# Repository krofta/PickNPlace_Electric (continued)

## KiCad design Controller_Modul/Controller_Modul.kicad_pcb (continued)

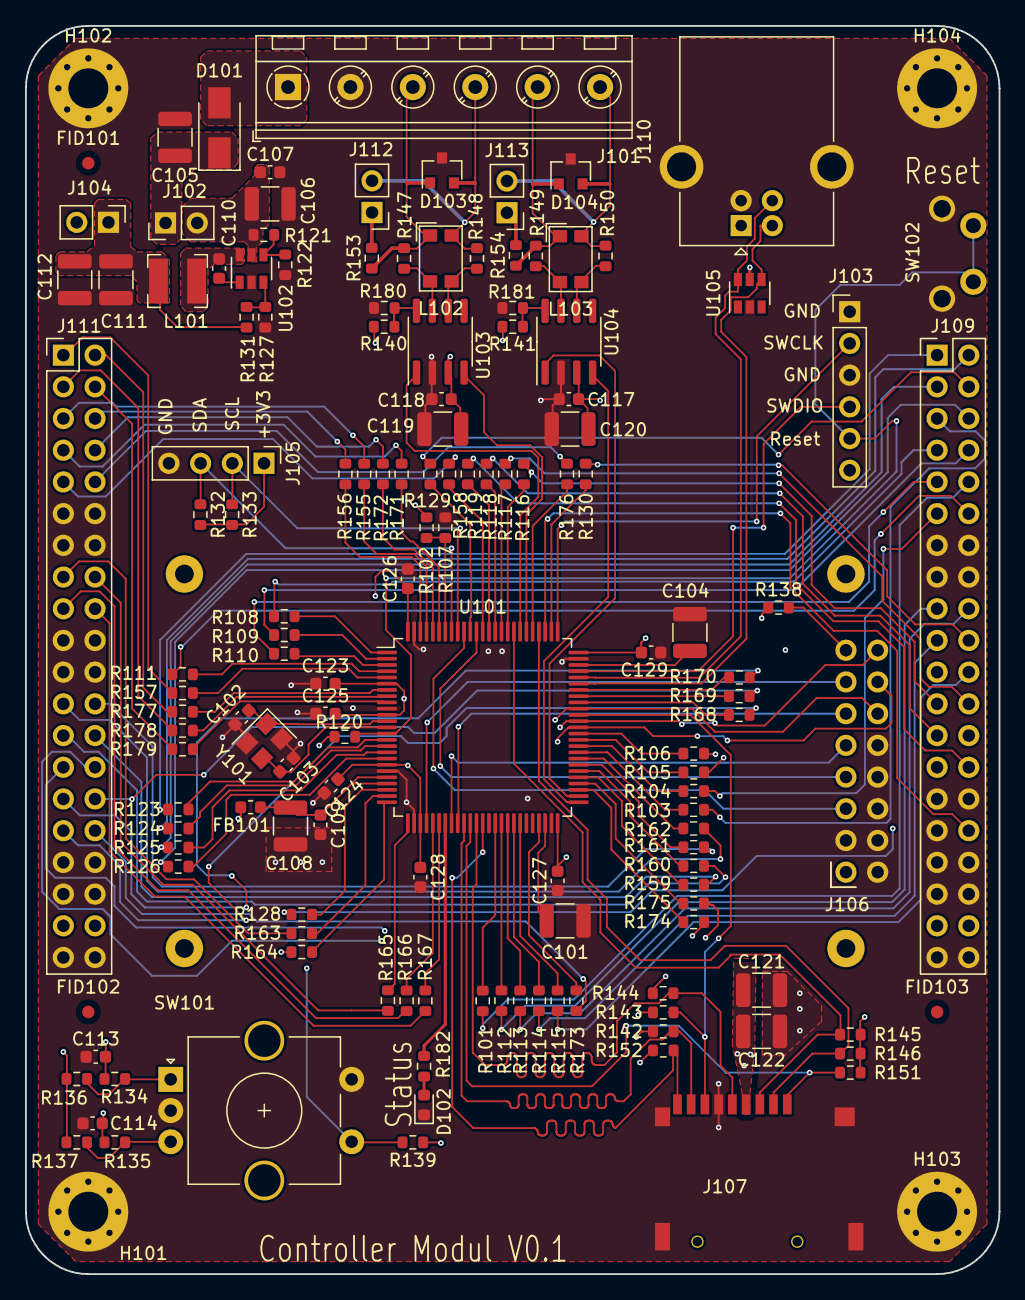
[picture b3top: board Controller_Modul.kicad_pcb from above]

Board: 4 copper layers, 78.0 x 100.0 mm, 147 parts (0 on the bottom side), 158 nets.

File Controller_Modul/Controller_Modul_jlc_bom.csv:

Comment,Designator,Footprint,LCSC Part #
"2.2u 50V Unpolarized capacitor, small symbol","C101,C104",C_1210_3225Metric, C696854 
"18p 50V Unpolarized capacitor, small symbol","C102,C103",C_0603_1608Metric,C258467
"10u 50V Unpolarized capacitor, small symbol","C105,C106,C108,C111,C112,C121,C122",C_1210_3225Metric,C1849
"100n 50V Unpolarized capacitor, small symbol","C107,C109,C110,C123,C124,C125,C126,C127,C128,C129",C_0603_1608Metric,C282519
"100n Unpolarized capacitor, small symbol","C113,C114,C117,C118",C_0603_1608Metric,C83060
"10u Unpolarized capacitor, small symbol","C119,C120",C_1210_3225Metric,C1849
"SS22F-SS2200F Schottky diode, small symbol",D101,D_SMA,C190803
"70R Ferrite bead, small symbol",FB101,L_0603_1608Metric,C513774
"Screw_Terminal_01x06 Generic screw terminal, single row, 01x06, script generated (kicad-library-utils/schlib/autogen/connector/)",J101,TerminalBlock_RND_205-00049_1x06_P5.00mm_Horizontal,C8475
"Conn_02x01 Generic connector, double row, 02x01, this symbol is compatible with counter-clockwise, top-bottom and odd-even numbering schemes., script generated (kicad-library-utils/schlib/autogen/connector/)","J102,J104,J112,J113",PinHeader_1x02_P2.54mm_Vertical,C358684
"Conn_01x08_Male Generic connector, double row, 02x08, top/bottom pin numbering scheme (row 1: 1...pins_per_row, row2: pins_per_row+1 ... num_pins), script generated (kicad-library-utils/schlib/autogen/connector/)",J106,ST7789_Waveshare2,C3406
Micro_SD_Card_Det Micro SD Card Socket with card detection pins,J107,TF-115-BCP9,C720505
IPC 16P ,J108,Empty,C8372
"Conn_02x20_Odd_Even Generic connector, double row, 02x20, odd/even pin numbering scheme (row 1 odd numbers, row 2 even numbers), script generated (kicad-library-utils/schlib/autogen/connector/)","J109,J111",PinHeader_2x20_P2.54mm_Vertical,C601944
USB_B_Mini USB Type B connector,J110,USB_B_OST_USB-B1HSxx_Horizontal,C46392
IPC 40P ,"J114,J115",Empty,C601933
"12u  SRN4018 Inductor, small symbol",L101,L_Bourns-SRN4018,C354591 
"1K Resistor, small symbol","R101,R103,R104,R105,R106,R108,R109,R110,R111,R112,R113,R114,R115,R116,R117,R118,R119,R123,R124,R125,R126,R128,R129,R130,R132,R133,R136,R137,R138,R139,R140,R141,R155,R156,R157,R158,R159,R160,R161,R162,R163,R164,R165,R166,R167,R168,R169,R170,R171,R172,R173,R174,R175,R176,R177,R178,R179",R_0603_1608Metric,C14676
"10K Resistor, small symbol","R107,R120,R134,R135,R152",R_0603_1608Metric,C99198
"51K Resistor, small symbol","R121,R122,R131",R_0603_1608Metric,C384211
"22K1 Resistor, small symbol","R127,R142,R143,R144,R145,R146,R151",R_0603_1608Metric,C137768
"0R Resistor, small symbol","R147,R148,R149,R150",R_0603_1608Metric,C384298
"120R Resistor, small symbol","R153,R154",R_0603_1608Metric,C114681
TPS560430 ,U102,SOT-23-6,C524782
"SN65HVD230 CAN Bus Transceivers, 3.3V, 1Mbps, Low-Power capabilities, SOIC-8","U103,U104",SOIC-8_3.9x4.9mm_P1.27mm,C12084
"SRV05-4 ESD Protection Diodes with Low Clamping Voltage, SOT-23-6",U105,SOT-23-6,C316033
"8MHz Four pin crystal, GND on pins 2 and 4",Y101,Crystal_SMD_3225-4Pin_3.2x2.5mm,C400090

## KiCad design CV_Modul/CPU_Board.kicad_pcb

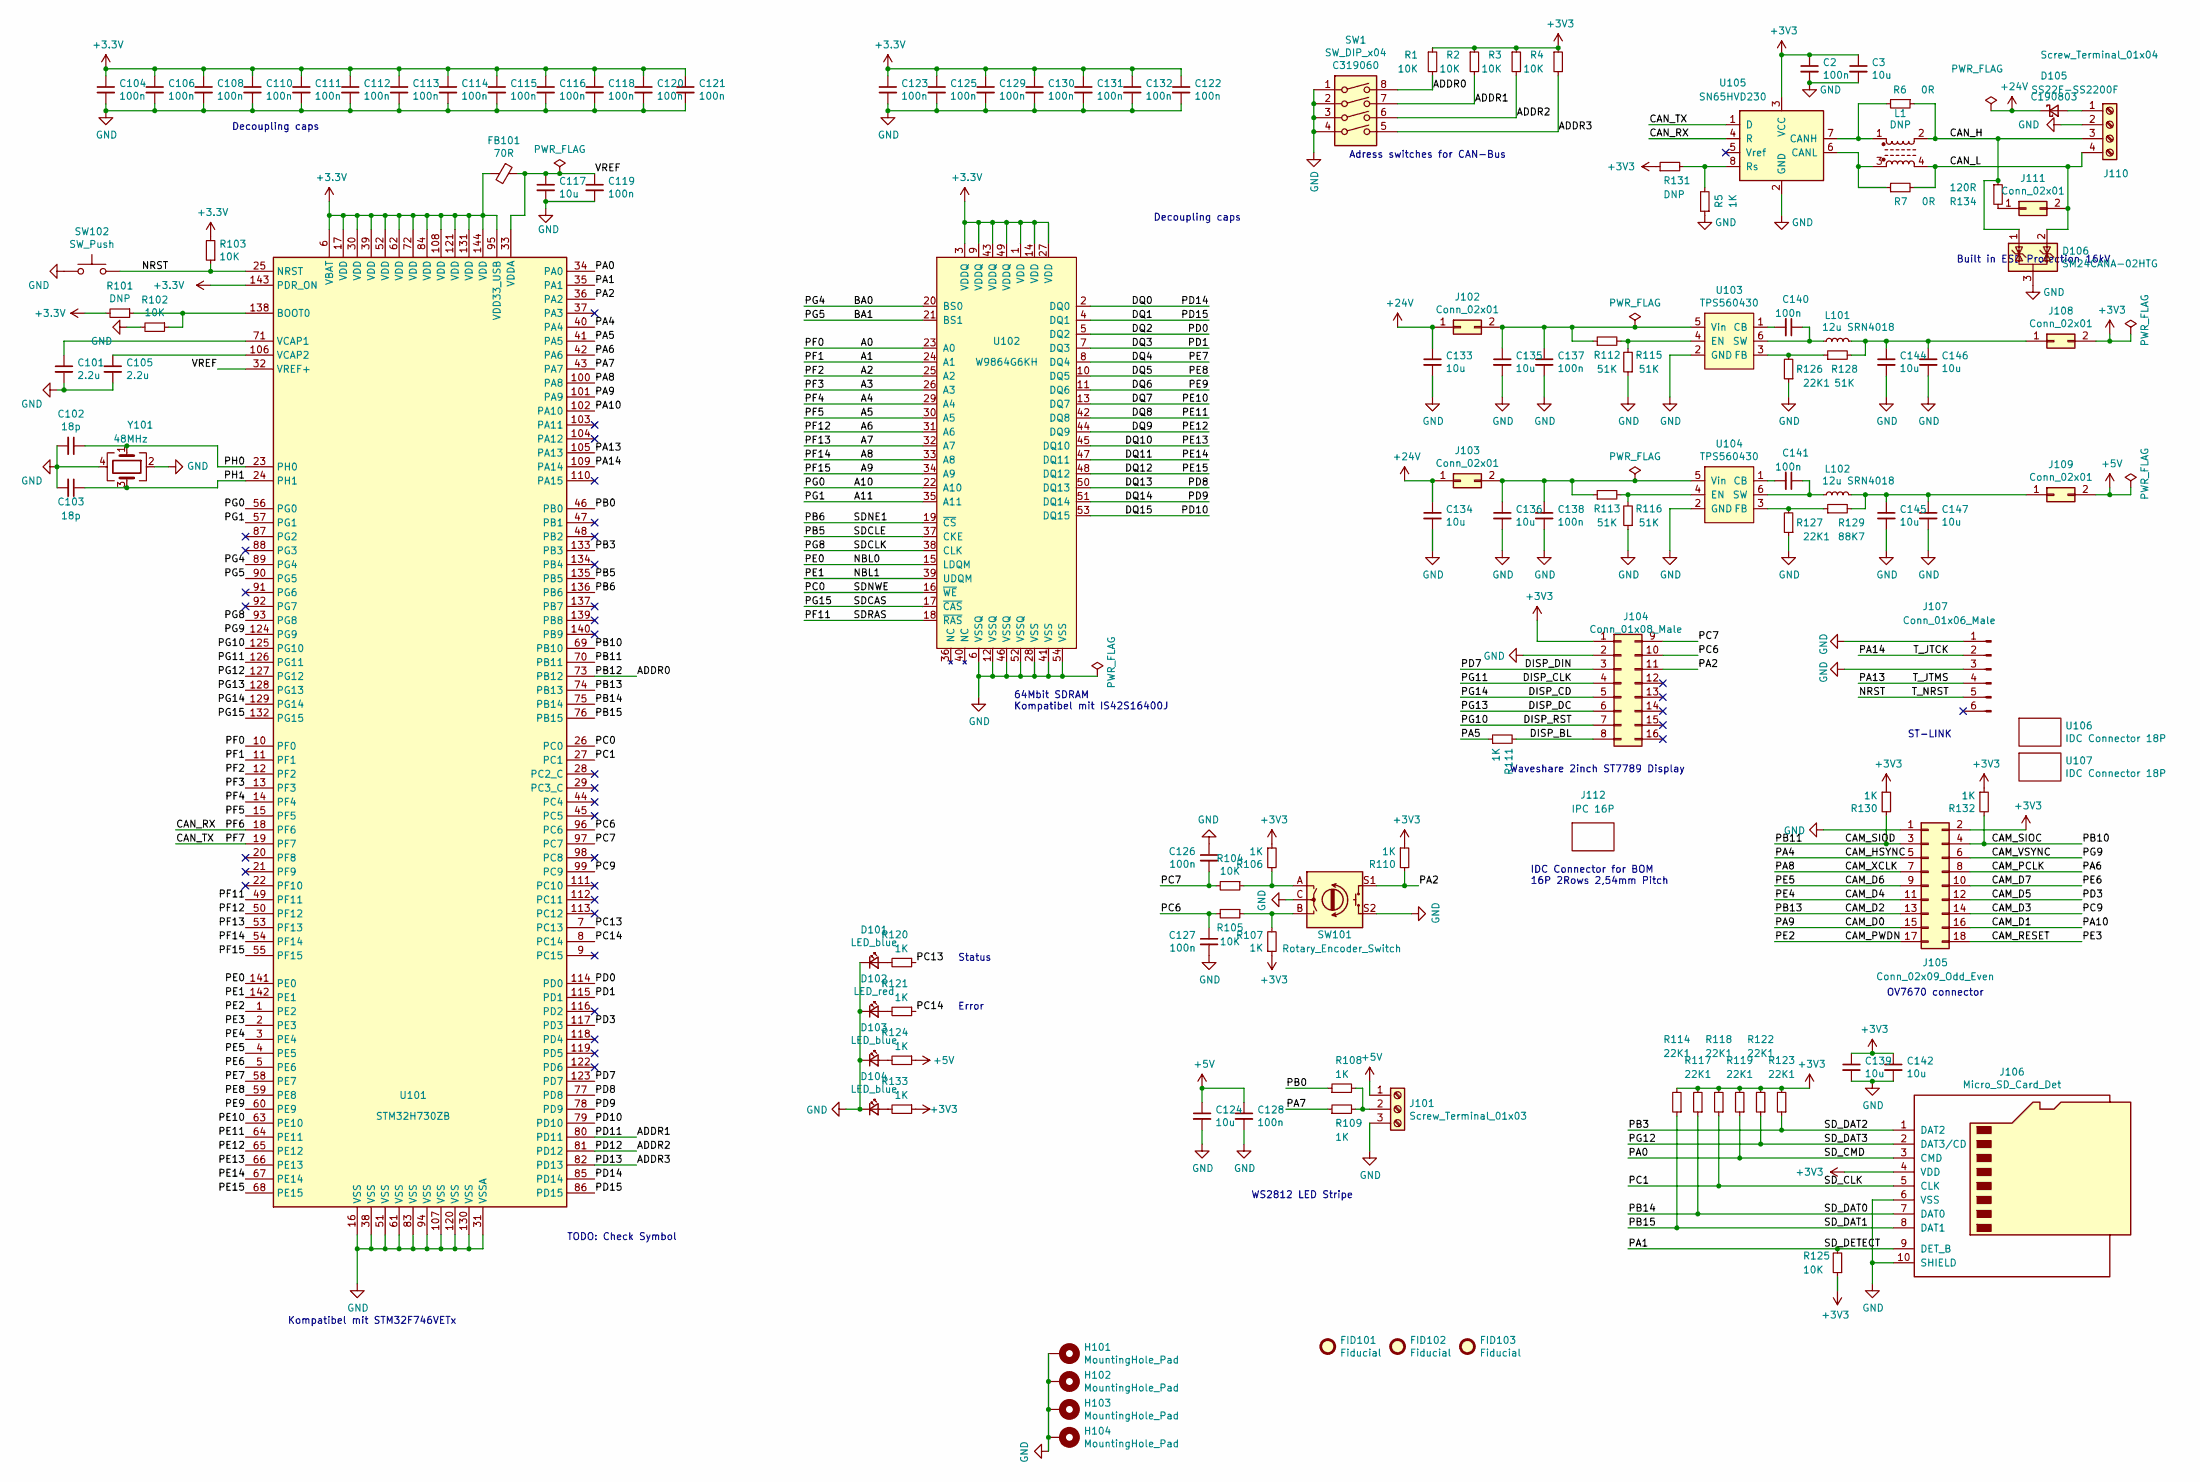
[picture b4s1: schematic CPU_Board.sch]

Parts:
C2, C104, C106, C108, C110, C111, C112, C113, C114, C115, C116, C118, C119, C120, C121, C122, C123, C125, C126, C127, C128, C129, C130, C131, C132, C137, C138, C140, C141: 100n; C_0603_1608Metric; LCSC C83060
C3, C117, C124, C133, C134, C135, C136, C139, C142, C144, C145, C146, C147: 10u; C_1210_3225Metric; LCSC C1849
C101, C105: 2.2u; C_1210_3225Metric; LCSC C696854
C102, C103: 18p; C_0603_1608Metric; LCSC C258467
D101, D103, D104: LED_blue; LED_0603_1608Metric; LCSC C193191
D102: LED_red; LED_0603_1608Metric; LCSC C205445
D105: SS22F-SS2200F; D_SMA; LCSC C190803
D106: SM24CANA-02HTG; SOT-23; LCSC C151236
FB101: 70R; L_0603_1608Metric; LCSC C513774
FID101, FID102, FID103: Fiducial; Fiducial_1mm_Mask2mm; LCSC 0
H101, H102, H103, H104: MountingHole_Pad; MountingHole_3.2mm_M3_Pad_Via; LCSC 0
J101: Screw_Terminal_01x03; TerminalBlock_RND_205-00046_1x03_P5.00mm_Horizontal; LCSC C8401
J102, J103, J108, J109, J111: Conn_02x01; PinHeader_1x02_P2.54mm_Vertical; LCSC 0
J104: Conn_01x08_Male; ST7789_Waveshare; LCSC 0
J105: Conn_02x09_Odd_Even; PinHeader_2x09_P2.54mm_Vertical; LCSC C11216
J106: Micro_SD_Card_Det; TF-115-BCP9; LCSC C720505
J107: Conn_01x06_Male; PinHeader_1x06_P2.54mm_Vertical; LCSC 0
J110: Screw_Terminal_01x04; TerminalBlock_RND_205-00047_1x04_P5.00mm_Horizontal; LCSC C8475
J112: IPC 16P; Empty; LCSC C8372
L1: DNP; L_CommonModeChoke_Coilcraft_1812CAN; LCSC 0
L101, L102: 12u SRN4018; L_Bourns-SRN4018; LCSC C354591
R1, R2, R3, R4, R102, R103, R104, R105, R125: 10K; R_0603_1608Metric; LCSC C99198
R5, R106, R107, R108, R109, R110, R111, R120, R121, R124, R130, R132, R133: 1K; R_0603_1608Metric; LCSC C14676
R6, R7: 0R; R_0603_1608Metric; LCSC C384298
R101, R131: DNP; R_0603_1608Metric; LCSC 0
R112, R113, R115, R116, R128: 51K; R_0603_1608Metric; LCSC C384211
R114, R117, R118, R119, R122, R123, R126, R127: 22K1; R_0603_1608Metric; LCSC C137768
R129: 88K7; R_0603_1608Metric; LCSC C163418
R134: 120R; R_0603_1608Metric; LCSC C114681
SW1: SW_DIP_x04; SW_DIP_SPSTx04_Slide_6.7x11.72mm_W7.62mm_P2.54mm_LowProfile; LCSC C319060
SW101: Rotary_Encoder_Switch; RotaryEncoder_Alps_EC11E-Switch_Vertical_H20mm_CircularMoun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; LCSC 0
SW102: SW_Push; TactileSwitchLCSC; LCSC C455137
U101: STM32H730ZB; LQFP-144_20x20mm_P0.5mm; LCSC 0
U102: W9864G6KH; TSOP-II-54_22.2x10.16mm_P0.8mm; LCSC C62378
U103, U104: TPS560430; SOT-23-6; LCSC C524782
U105: SN65HVD230; SOIC-8_3.9x4.9mm_P1.27mm; LCSC C12084
U106, U107: IDC Connector 18P; Empty; LCSC C376143
Y101: 48MHz; Crystal_SMD_3225-4Pin_3.2x2.5mm; LCSC C389928

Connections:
+5V: C124.1, C128.1, J101.1, J109.2, R124.1
+24V: C133.1, C134.1, D105.1 (K), J102.1, J103.1
/A0: U101.10 (PF0), U102.23 (A0)
/A1: U101.11 (PF1), U102.24 (A1)
/A2: U101.12 (PF2), U102.25 (A2)
/A3: U101.13 (PF3), U102.26 (A3)
/A4: U101.14 (PF4), U102.29 (A4)
/A5: U101.15 (PF5), U102.30 (A5)
/A6: U101.50 (PF12), U102.31 (A6)
/A7: U101.53 (PF13), U102.32 (A7)
/A8: U101.54 (PF14), U102.33 (A8)
/A9: U101.55 (PF15), U102.34 (A9)
/A10: U101.56 (PG0), U102.22 (A10)
/A11: U101.57 (PG1), U102.35 (A11)
/ADDR0: R1.2, SW1.8, U101.73 (PB12)
/ADDR1: R2.2, SW1.7, U101.80 (PD11)
/ADDR2: R3.2, SW1.6, U101.81 (PD12)
/ADDR3: R4.2, SW1.5, U101.82 (PD13)
/BA0: U101.89 (PG4), U102.20 (BS0)
/BA1: U101.90 (PG5), U102.21 (BS1)
/CAM_D0: J105.15, U101.101 (PA9)
/CAM_D1: J105.16, U101.102 (PA10)
/CAM_D2: J105.13, U101.74 (PB13)
/CAM_D3: J105.14, U101.99 (PC9)
/CAM_D4: J105.11, U101.3 (PE4)
/CAM_D5: J105.12, U101.117 (PD3)
/CAM_D6: J105.9, U101.4 (PE5)
/CAM_D7: J105.10, U101.5 (PE6)
/CAM_HSYNC: J105.5, U101.40 (PA4)
/CAM_PCLK: J105.8, U101.42 (PA6)
/CAM_PWDN: J105.17, U101.1 (PE2)
/CAM_RESET: J105.18, U101.2 (PE3)
/CAM_SIOC: J105.4, R132.2, U101.69 (PB10)
/CAM_SIOD: J105.3, R130.2, U101.70 (PB11)
/CAM_VSYNC: J105.6, U101.124 (PG9)
/CAM_XCLK: J105.7, U101.100 (PA8)
/CAN_H: D106.1 (K), J110.3, L1.2, R6.1, R134.1
/CAN_L: D106.2 (K), J110.4, J111.2, L1.4, R7.2
/CAN_RX: U101.18 (PF6), U105.4 (R)
/CAN_TX: U101.19 (PF7), U105.1 (D)
/DISP_BL: J104.8, R111.2
/DISP_CD: J104.5, U101.129 (PG14)
/DISP_CLK: J104.4, U101.126 (PG11)
/DISP_DC: J104.6, U101.128 (PG13)
/DISP_DIN: J104.3, U101.123 (PD7)
/DISP_RST: J104.7, U101.125 (PG10)
/DQ0: U101.85 (PD14), U102.2 (DQ0)
/DQ1: U101.86 (PD15), U102.4 (DQ1)
/DQ2: U101.114 (PD0), U102.5 (DQ2)
/DQ3: U101.115 (PD1), U102.7 (DQ3)
/DQ4: U101.58 (PE7), U102.8 (DQ4)
/DQ5: U101.59 (PE8), U102.10 (DQ5)
/DQ6: U101.60 (PE9), U102.11 (DQ6)
/DQ7: U101.63 (PE10), U102.13 (DQ7)
/DQ8: U101.64 (PE11), U102.42 (DQ8)
/DQ9: U101.65 (PE12), U102.44 (DQ9)
/DQ10: U101.66 (PE13), U102.45 (DQ10)
/DQ11: U101.67 (PE14), U102.47 (DQ11)
/DQ12: U101.68 (PE15), U102.48 (DQ12)
/DQ13: U101.77 (PD8), U102.50 (DQ13)
/DQ14: U101.78 (PD9), U102.51 (DQ14)
/DQ15: U101.79 (PD10), U102.53 (DQ15)
/NBL0: U101.141 (PE0), U102.15 (LDQM)
/NBL1: U101.142 (PE1), U102.39 (UDQM)
/NRST: J107.5, R103.1, SW102.2, U101.25 (NRST)
/PA0: J106.3 (CMD), R119.1, U101.34 (PA0)
/PA1: J106.9 (DET_B), R125.2, U101.35 (PA1)
/PA2: J104.11, R110.2, SW101.S1, U101.36 (PA2)
/PA5: R111.1, U101.41 (PA5)
/PA7: R109.1, U101.43 (PA7)
/PA13: J107.4, U101.105 (PA13)
/PA14: J107.2, U101.109 (PA14)
/PB0: R108.1, U101.46 (PB0)
/PB3: J106.1 (DAT2), R123.1, U101.133 (PB3)
/PB5: U101.135 (PB5), U102.37 (CKE)
/PB6: U101.136 (PB6), U102.19 (~CS)
/PB14: J106.7 (DAT0), R117.1, U101.75 (PB14)
/PB15: J106.8 (DAT1), R114.1, U101.76 (PB15)
/PC0: U101.26 (PC0), U102.16 (~WE)
/PC1: J106.5 (CLK), R118.1, U101.27 (PC1)
/PC6: C127.1, J104.10, R105.2, U101.96 (PC6)
/PC7: C126.2, J104.9, R104.2, U101.97 (PC7)
/PC13: R120.1, U101.7 (PC13)
/PC14: R121.1, U101.8 (PC14)
/PF11: U101.49 (PF11), U102.18 (~RAS)
/PG8: U101.93 (PG8), U102.38 (CLK)
/PG12: J106.2 (DAT3/CD), R122.1, U101.127 (PG12)
/PG15: U101.132 (PG15), U102.17 (~CAS)
/PH0: C102.1, U101.23 (PH0), Y101.1
/PH1: C103.1, U101.24 (PH1), Y101.3
/VREF: C117.1, C119.1, FB101.1, U101.32 (VREF+), U101.33 (VDDA)
GND: C2.2, C3.2, C101.2, C102.2, C103.2, C104.2, C105.2, C106.2, C108.2, C110.2, C111.2, C112.2, C113.2, C114.2, C115.2, C116.2, C117.2, C118.2, C119.2, C120.2, C121.2, C122.2, C123.2, C124.2, C125.2, C126.1, C127.2, C128.2, C129.2, C130.2, C131.2, C132.2, C133.2, C134.2, C135.2, C136.2, C137.2, C138.2, C139.2, C142.2, C144.2, C145.2, C146.2, C147.2, D101.1 (K), D102.1 (K), D103.1 (K), D104.1 (K), D106.3 (A), H101.1, H102.1, H103.1, H104.1, J101.3, J104.2, J105.1, J106.6 (VSS), J106.10 (SHIELD), J107.1, J107.3, J110.2, R5.1, R102.2, R115.1, R116.1, R126.1, R127.1, SW1.1, SW1.2, SW1.3, SW1.4, SW101.C, SW101.S2, SW102.1, U101.16 (VSS), U101.31 (VSSA), U101.38 (VSS), U101.51 (VSS), U101.61 (VSS), U101.83 (VSS), U101.94 (VSS), U101.107 (VSS), U101.120 (VSS), U101.130 (VSS), U102.6 (VSSQ), U102.12 (VSSQ), U102.28 (VSS), U102.41 (VSS), U102.46 (VSSQ), U102.52 (VSSQ), U102.54 (VSS), U103.2 (GND), U104.2 (GND), U105.2 (GND), Y101.2, Y101.4
unnamed: C101.1, U101.71 (VCAP1)
unnamed: C105.1, U101.106 (VCAP2)
unnamed: C135.1, C137.1, J102.2, R112.1, U103.5 (Vin)
unnamed: C136.1, C138.1, J103.2, R113.1, U104.5 (Vin)
unnamed: C140.1, L101.1, U103.6 (SW)
unnamed: C140.2, U103.1 (CB)
unnamed: C141.1, L102.1, U104.6 (SW)
unnamed: C141.2, U104.1 (CB)
unnamed: C144.1, C146.1, J108.1, L101.2, R128.2
unnamed: C145.1, C147.1, J109.1, L102.2, R129.2
unnamed: D101.2 (A), R120.2
unnamed: D102.2 (A), R121.2
unnamed: D103.2 (A), R124.2
unnamed: D104.2 (A), R133.2
unnamed: D105.2 (A), J110.1
unnamed: J101.2, R108.2, R109.2
unnamed: J111.1, R134.2
unnamed: L1.1, R6.2, U105.7 (CANH)
unnamed: L1.3, R7.1, U105.6 (CANL)
unnamed: R101.1, R102.1, U101.138 (BOOT0)
unnamed: R104.1, R106.2, SW101.A
unnamed: R105.1, R107.2, SW101.B
unnamed: R112.2, R115.2, U103.4 (EN)
unnamed: R113.2, R116.2, U104.4 (EN)
unnamed: R126.2, R128.1, U103.3 (FB)
unnamed: R127.2, R129.1, U104.3 (FB)
unnamed: R5.2, R131.2, U105.8 (Rs)

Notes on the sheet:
64Mbit SDRAM Kompatibel mit IS42S16400J
Kompatibel mit STM32F746VETx
TODO: Check Symbol
Decoupling caps
ST-LINK
OV7670 connector
Waveshare 2inch ST7789 Display
WS2812 LED Stripe
Status
Error
Adress switches for CAN-Bus
Built in ESD Protection 16kV
IDC Connector for BOM 16P 2Rows 2,54mm Pitch

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
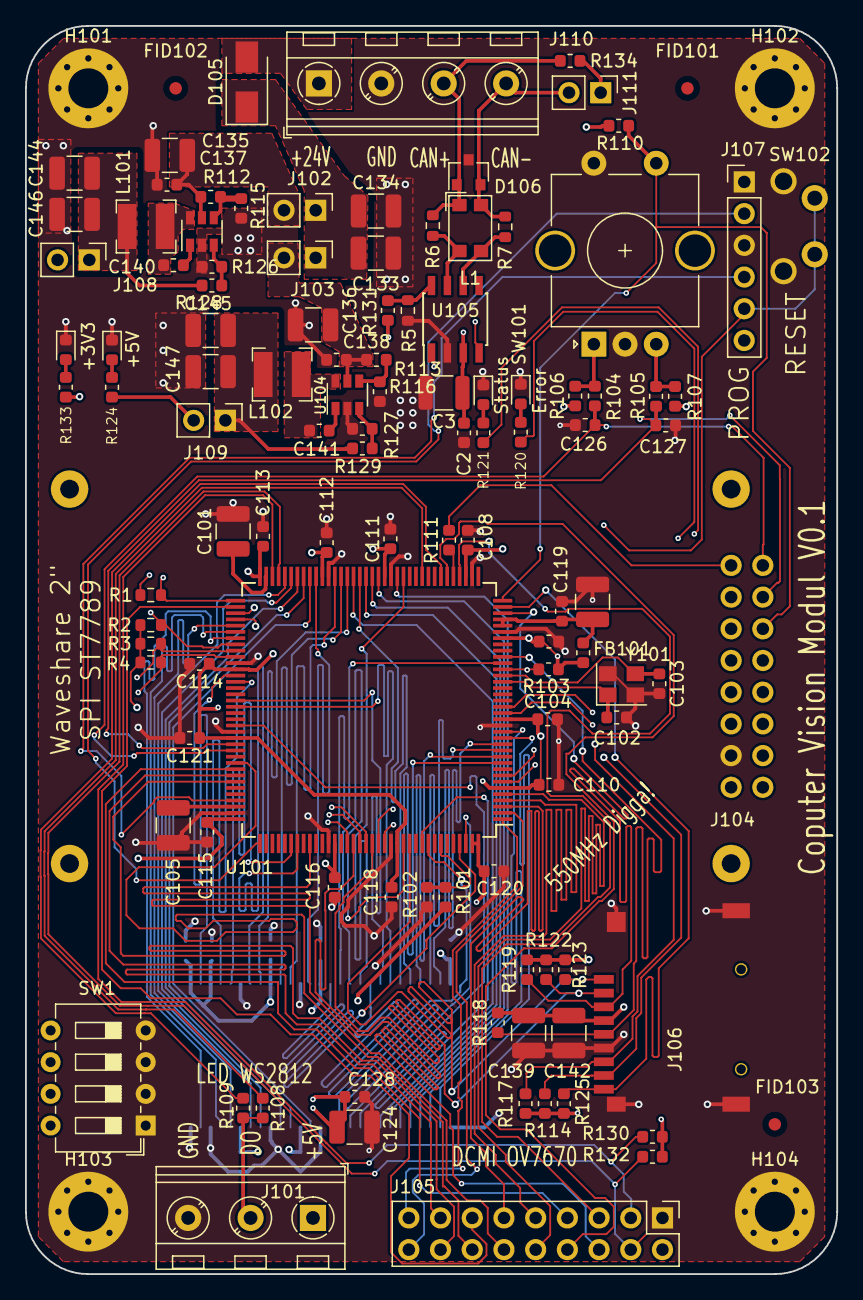
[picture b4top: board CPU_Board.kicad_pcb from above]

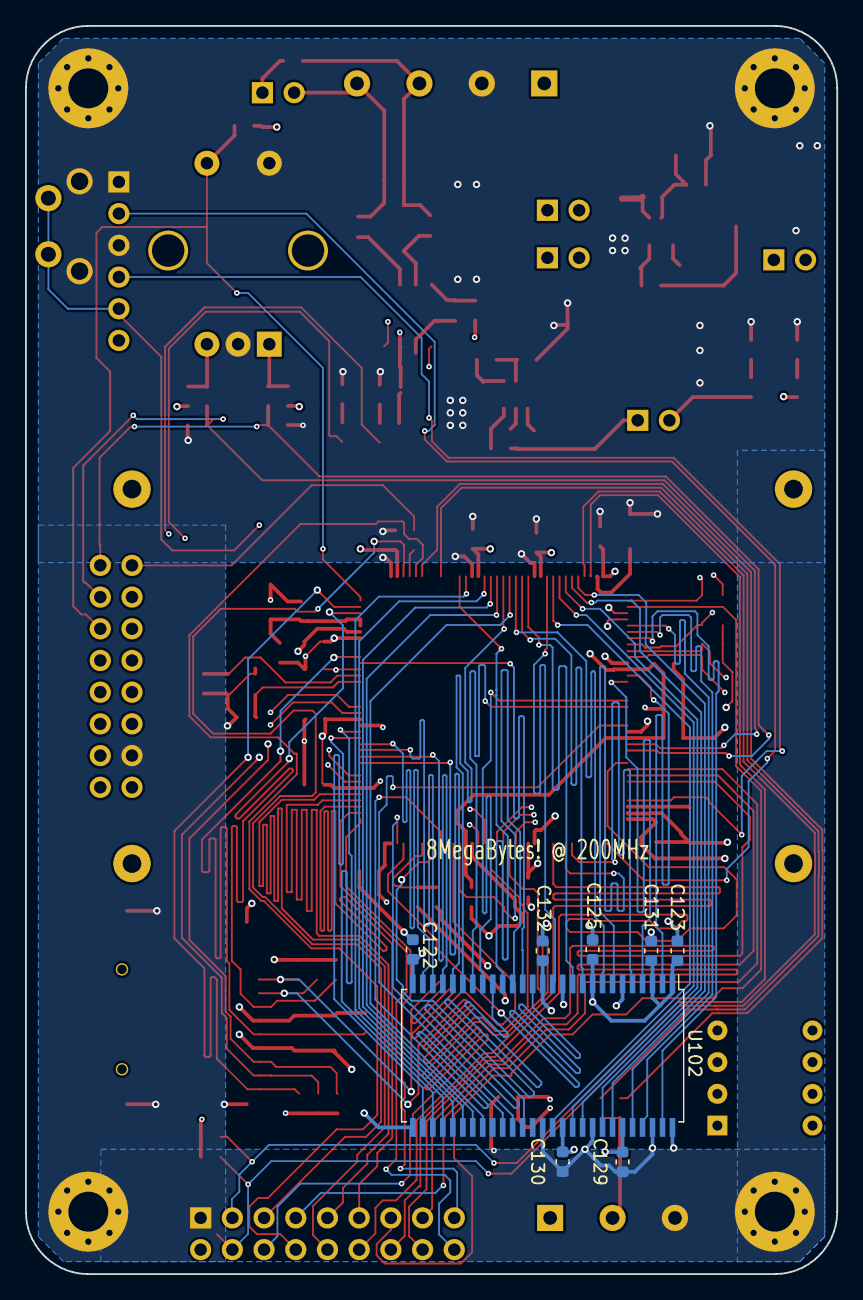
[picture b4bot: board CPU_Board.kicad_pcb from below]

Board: 4 copper layers, 65.0 x 100.0 mm, 127 parts (8 on the bottom side), 120 nets.

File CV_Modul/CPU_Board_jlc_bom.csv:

Comment,Designator,Footprint,LCSC Part #
"100n Unpolarized capacitor, small symbol","C2,C104,C106,C108,C110,C111,C112,C113,C114,C115,C116,C118,C119,C120,C121,C122,C123,C125,C126,C127,C128,C129,C130,C131,C132,C137,C138,C140,C141",C_0603_1608Metric,C83060
"10u Unpolarized capacitor, small symbol","C3,C117,C124,C133,C134,C135,C136,C139,C142,C144,C145,C146,C147",C_1210_3225Metric,C1849
"2.2u Unpolarized capacitor, small symbol","C101,C105",C_1210_3225Metric, C696854 
"18p Unpolarized capacitor, small symbol","C102,C103",C_0603_1608Metric,C258467
"LED_blue Light emitting diode, small symbol","D101,D103,D104",LED_0603_1608Metric,C193191
"LED_red Light emitting diode, small symbol",D102,LED_0603_1608Metric,C205445
"SS22F-SS2200F Schottky diode, small symbol",D105,D_SMA,C190803
"70R Ferrite bead, small symbol",FB101,L_0603_1608Metric,C513774
"Screw_Terminal_01x03 Generic screw terminal, single row, 01x03, script generated (kicad-library-utils/schlib/autogen/connector/)",J101,TerminalBlock_RND_205-00046_1x03_P5.00mm_Horizontal,C8401
"Conn_02x09_Odd_Even Generic connector, double row, 02x09, odd/even pin numbering scheme (row 1 odd numbers, row 2 even numbers), script generated (kicad-library-utils/schlib/autogen/connector/)",J105,PinHeader_2x09_P2.54mm_Vertical,C11216
Micro_SD_Card_Det Micro SD Card Socket with card detection pins,J106,TF-115-BCP9,C720505
"Screw_Terminal_01x04 Generic screw terminal, single row, 01x04, script generated (kicad-library-utils/schlib/autogen/connector/)",J110,TerminalBlock_RND_205-00047_1x04_P5.00mm_Horizontal,C8475 
IPC 16P ,J112,Empty,C8372
"12u  SRN4018 Inductor, small symbol","L101,L102",L_Bourns-SRN4018,C354591 
"10K Resistor, small symbol","R1,R2,R3,R4,R5,R102,R103,R104,R105,R125,R131",R_0603_1608Metric,C99198
"0R Resistor, small symbol","R6,R7",R_0603_1608Metric,C384298
"1K Resistor, small symbol","R106,R107,R108,R109,R110,R111,R120,R121,R124,R130,R132,R133",R_0603_1608Metric,C14676
"51K Resistor, small symbol","R112,R113,R115,R116,R128",R_0603_1608Metric,C384211
"22K1 Resistor, small symbol","R114,R117,R118,R119,R122,R123,R126,R127",R_0603_1608Metric,C137768
"88K7 Resistor, small symbol",R129,R_0603_1608Metric,C163418
"120R Resistor, small symbol",R134,R_0603_1608Metric,C114681
"SW_DIP_x04 4x DIP Switch, Single Pole Single Throw (SPST) switch, small symbol",SW1,SW_DIP_SPSTx04_Slide_6.7x11.72mm_W7.62mm_P2.54mm_LowProfile,C319060
W9864G6KH ,U102,TSOP-II-54_22.2x10.16mm_P0.8mm,C62378
TPS560430 ,"U103,U104",SOT-23-6,C524782
"SN65HVD230 CAN Bus Transceivers, 3.3V, 1Mbps, Low-Power capabilities, SOIC-8",U105,SOIC-8_3.9x4.9mm_P1.27mm,C12084
IDC Connector 18P ,"U106,U107",Empty,C376143
"48MHz Four pin crystal, GND on pins 2 and 4",Y101,Crystal_SMD_3225-4Pin_3.2x2.5mm,C389928

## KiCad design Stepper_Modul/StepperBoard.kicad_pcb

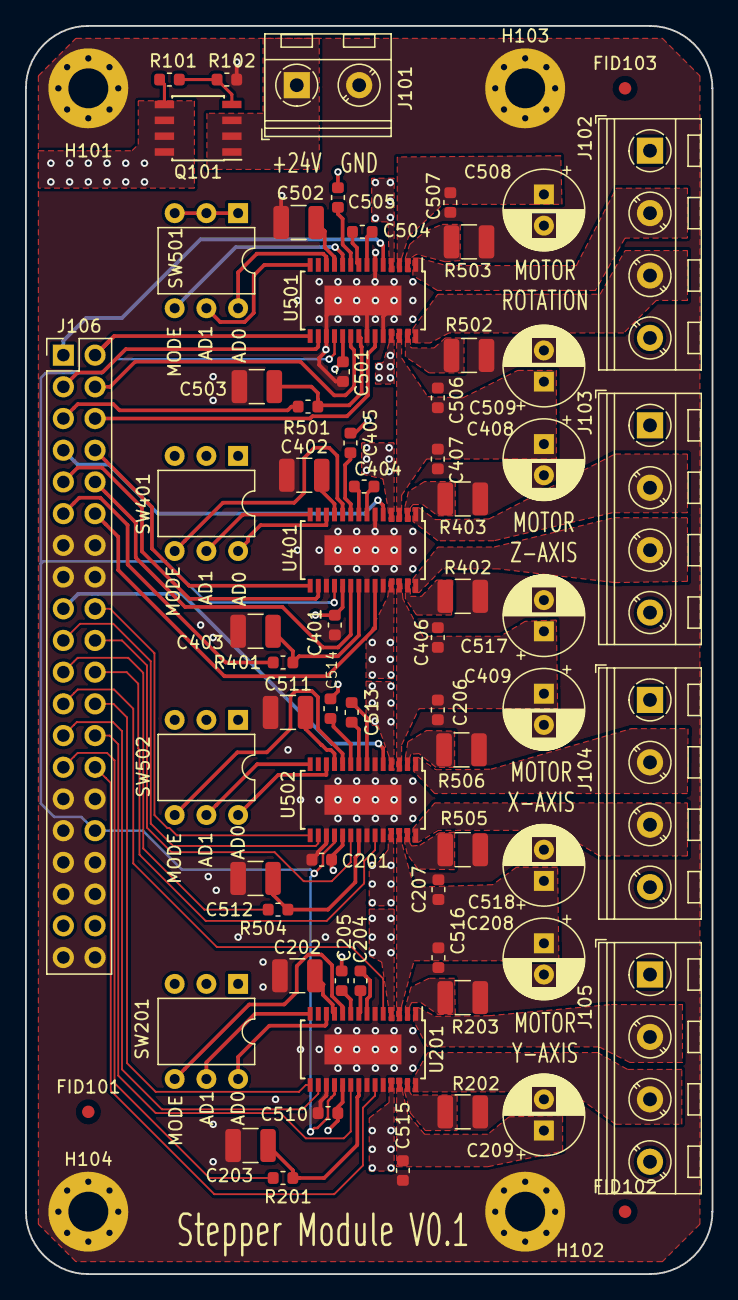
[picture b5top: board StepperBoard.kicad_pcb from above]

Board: 4 copper layers, 55.0 x 100.0 mm, 72 parts (0 on the bottom side), 86 nets.

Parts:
C201, C205, C206, C207, C401, C405, C406, C407, C501, C505, C506, C507, C510, C514, C515, C516: 100n 50V; C_0603_1608Metric
C202, C203, C402, C403, C502, C503, C511, C512: 2.2u 50V; C_1210_3225Metric
C204, C404, C504, C513: 22n 50V; C_0603_1608Metric
C208, C209, C408, C409, C508, C509, C517, C518: 100u 35V; CP_Radial_D6.3mm_P2.50mm
FID101, FID102, FID103: Fiducial; Fiducial_1mm_Mask2mm
H101, H102, H103, H104: MountingHole_Pad; MountingHole_3.2mm_M3_Pad_Via
J101: Screw_Terminal_01x02; TerminalBlock_RND_205-00045_1x02_P5.00mm_Horizontal
J102, J103, J104, J105: Screw_Terminal_01x04; TerminalBlock_RND_205-00047_1x04_P5.00mm_Horizontal
J106: Conn_02x20_Odd_Even; PinHeader_2x20_P2.54mm_Vertical
Q101: Si4431CDY; SOIC-8_3.9x4.9mm_P1.27mm
R101, R102, R201, R401, R501, R504: 22K1; R_0603_1608Metric
R202, R203, R402, R403, R502, R503: 0.1R 0.5W; R_1210_3225Metric
R505, R506: 0.22R 0.5W; R_1210_3225Metric
SW201, SW401, SW501, SW502: SW_DIP_x03; DIP-6_W7.62mm
U201, U401, U501, U502: TMC2226; TSSOP-28-1EP_4.4x9.7mm_P0.65mm

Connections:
+3V3: C201.2, C401.2, C501.2, C510.2, J106.37, J106.38, SW201.1, SW201.2, SW201.3, SW401.1, SW401.2, SW401.3, SW501.1, SW501.2, SW501.3, SW502.1, SW502.2, SW502.3, U201.19, U401.19, U501.19, U502.19
+24V: C205.2, C206.2, C207.2, C208.1, C209.1, C405.2, C406.2, C407.2, C408.1, C409.1, C505.2, C506.2, C507.2, C508.1, C509.1, C514.2, C515.2, C516.2, C517.1, C518.1, Q101.5, Q101.6, Q101.7, Q101.8, R101.2, U201.3, U201.26, U401.3, U401.26, U501.3, U501.26, U502.3, U502.26
/CUR_ROT: J106.5, R501.2
/CUR_X: J106.21, R504.2
/CUR_Y: J106.27, R201.2
/CUR_Z: J106.11, R401.2
/DIAG_ROT: J106.2, U501.15
/DIAG_X: J106.18, U502.15
/DIAG_Y: J106.24, U201.15
/DIAG_Z: J106.8, U401.15
/DIR_ROT: J106.6, U501.23
/DIR_X: J106.22, U502.23
/DIR_Y: J106.28, U201.23
/DIR_Z: J106.12, U401.23
/EN_ROT: J106.1, U501.5
/EN_X: J106.17, U502.5
/EN_Y: J106.23, U201.5
/EN_Z: J106.7, U401.5
/INDEX_ROT: J106.3, U501.16
/INDEX_X: J106.19, U502.16
/INDEX_Y: J106.25, U201.16
/INDEX_Z: J106.9, U401.16
/SINGLE_WIRE: J106.32, U201.18, U401.18, U501.18, U502.18
/STEP_ROT: J106.4, U501.20
/STEP_X: J106.20, U502.20
/STEP_Y: J106.26, U201.20
/STEP_Z: J106.10, U401.20
/Stepper_rotation/5VOUT: C502.2, U501.11
/Stepper_rotation/OA1_ROT: J102.3, U501.28
/Stepper_rotation/OA2_ROT: J102.4, U501.25
/Stepper_rotation/OB1_ROT: J102.2, U501.1
/Stepper_rotation/OB2_ROT: J102.1, U501.4
/Stepper_x/5VOUT: C511.2, U502.11
/Stepper_x/OA1_X: J104.3, U502.28
/Stepper_x/OA2_X: J104.4, U502.25
/Stepper_x/OB1_X: J104.2, U502.1
/Stepper_x/OB2_X: J104.1, U502.4
/Stepper_y/5VOUT: C202.2, U201.11
/Stepper_y/OA1_Y: J105.3, U201.28
/Stepper_y/OA2_Y: J105.4, U201.25
/Stepper_y/OB1_Y: J105.2, U201.1
/Stepper_y/OB2_Y: J105.1, U201.4
/Stepper_z/5VOUT: C402.2, U401.11
/Stepper_z/OA1_Z: J103.3, U401.28
/Stepper_z/OA2_Z: J103.4, U401.25
/Stepper_z/OB1_Z: J103.2, U401.1
/Stepper_z/OB2_Z: J103.1, U401.4
GND: C201.1, C202.1, C203.1, C206.1, C207.1, C208.2, C209.2, C401.1, C402.1, C403.1, C406.1, C407.1, C408.2, C409.2, C501.1, C502.1, C503.1, C506.1, C507.1, C508.2, C509.2, C510.1, C511.1, C512.1, C515.1, C516.1, C517.2, C518.2, H101.1, H102.1, H103.1, H104.1, J101.2, J106.13, J106.14, J106.15, J106.16, J106.29, J106.30, J106.31, J106.33, J106.34, J106.35, J106.36, J106.39, J106.40, R102.1, R202.1, R203.1, R402.1, R403.1, R502.1, R503.1, R505.1, R506.1, U201.6, U201.17, U201.22, U201.24, U201.29, U401.6, U401.17, U401.22, U401.24, U401.29, U501.6, U501.17, U501.22, U501.24, U501.29, U502.6, U502.17, U502.22, U502.24, U502.29
unnamed: C203.2, R201.1, U201.21
unnamed: C204.1, U201.8
unnamed: C204.2, U201.7
unnamed: C205.1, U201.9
unnamed: C403.2, R401.1, U401.21
unnamed: C404.1, U401.8
unnamed: C404.2, U401.7
unnamed: C405.1, U401.9
unnamed: C503.2, R501.1, U501.21
unnamed: C504.1, U501.8
unnamed: C504.2, U501.7
unnamed: C505.1, U501.9
unnamed: C512.2, R504.1, U502.21
unnamed: C513.1, U502.8
unnamed: C513.2, U502.7
unnamed: C514.1, U502.9
unnamed: J101.1, Q101.1, Q101.2, Q101.3
unnamed: Q101.4, R101.1, R102.2
unnamed: R202.2, U201.27
unnamed: R203.2, U201.2
unnamed: R402.2, U401.27
unnamed: R403.2, U401.2
unnamed: R502.2, U501.27
unnamed: R503.2, U501.2
unnamed: R505.2, U502.27
unnamed: R506.2, U502.2
unnamed: SW201.4, U201.10
unnamed: SW201.5, U201.14
unnamed: SW201.6, U201.12
unnamed: SW401.4, U401.10
unnamed: SW401.5, U401.14
unnamed: SW401.6, U401.12
unnamed: SW501.4, U501.10
unnamed: SW501.5, U501.14
unnamed: SW501.6, U501.12
unnamed: SW502.4, U502.10
unnamed: SW502.5, U502.14
unnamed: SW502.6, U502.12

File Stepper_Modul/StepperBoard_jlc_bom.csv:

Comment,Designator,Footprint,LCSC Part #,Quantity
"100n 50V Unpolarized capacitor, small symbol","C201,C205,C206,C207,C401,C405,C406,C407,C501,C505,C506,C507,C510,C514,C515,C516",C_0603_1608Metric,C282519,16
"2.2u 50V Unpolarized capacitor, small symbol","C202,C203,C402,C403,C502,C503,C511,C512",C_1210_3225Metric, C696854 ,8
"22n 50V Unpolarized capacitor, small symbol","C204,C404,C504,C513",C_0603_1608Metric,C84712,4
"100u 35V Polarized capacitor, small symbol","C208,C209,C408,C409,C508,C509,C517,C518",CP_Radial_D6.3mm_P2.50mm,C45075,8
"Screw_Terminal_01x02 Generic screw terminal, single row, 01x02, script generated (kicad-library-utils/schlib/autogen/connector/)",J101,TerminalBlock_RND_205-00045_1x02_P5.00mm_Horizontal,C8475,1
"Screw_Terminal_01x04 Generic screw terminal, single row, 01x04, script generated (kicad-library-utils/schlib/autogen/connector/)","J102,J103,J104,J105",TerminalBlock_RND_205-00047_1x04_P5.00mm_Horizontal,C8475,4
"Conn_02x20_Odd_Even Generic connector, double row, 02x20, odd/even pin numbering scheme (row 1 odd numbers, row 2 even numbers), script generated (kicad-library-utils/schlib/autogen/connector/)",J106,PinHeader_2x20_P2.54mm_Vertical,C601944,1
"Si4431CDY P-MOSFET transistor, drain/gate/source",Q101,SOIC-8_3.9x4.9mm_P1.27mm,C144845,1
"22K1 Resistor, small symbol","R101,R102,R201,R401,R501,R504",R_0603_1608Metric,C137768,6
"0.1R 0.5W Resistor, small symbol","R202,R203,R402,R403,R502,R503",R_1210_3225Metric,C270892,6
"0.22R 0.5W Resistor, small symbol","R505,R506",R_1210_3225Metric,C159293,2
"SW_DIP_x03 3x DIP Switch, Single Pole Single Throw (SPST) switch, small symbol","SW201,SW401,SW501,SW502",DIP-6_W7.62mm,C52648,4
TMC2226 ,"U201,U401,U501,U502",TSSOP-28-1EP_4.4x9.7mm_P0.65mm,C705366,4

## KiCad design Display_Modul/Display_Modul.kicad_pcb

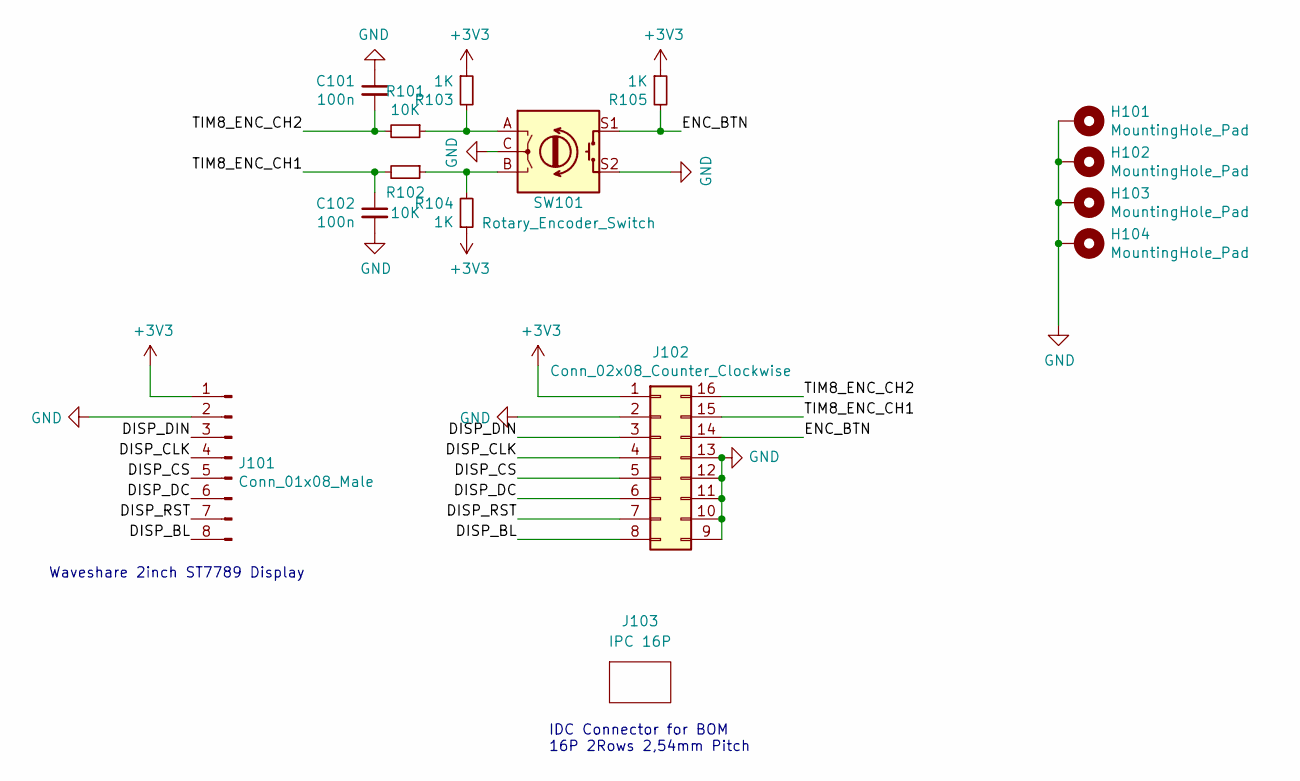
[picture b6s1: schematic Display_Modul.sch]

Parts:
C101, C102: 100n; C_0603_1608Metric; LCSC C83060
H101, H102, H103, H104: MountingHole_Pad; MountingHole_3.2mm_M3_Pad_Via; LCSC 0
J101: Conn_01x08_Male; ST7789_Waveshare; LCSC 0
J102: Conn_02x08_Counter_Clockwise; DisplayConnector; LCSC C3406
J103: IPC 16P; Empty; LCSC C8372
R101, R102: 10K; R_0603_1608Metric; LCSC C99198
R103, R104, R105: 1K; R_0603_1608Metric; LCSC C14676
SW101: Rotary_Encoder_Switch; RotaryEncoder_Alps_EC11E-Switch_Vertical_H20mm_CircularMoun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; LCSC C1322538

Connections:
+3V3: J101.1, J102.1, R103.1, R104.1, R105.1
/DISP_BL: J101.8, J102.8
/DISP_CLK: J101.4, J102.4
/DISP_CS: J101.5, J102.5
/DISP_DC: J101.6, J102.6
/DISP_DIN: J101.3, J102.3
/DISP_RST: J101.7, J102.7
/ENC_BTN: J102.14, R105.2, SW101.S1
/TIM8_ENC_CH1: C102.1, J102.15, R102.2
/TIM8_ENC_CH2: C101.2, J102.16, R101.2
GND: C101.1, C102.2, H101.1, H102.1, H103.1, H104.1, J101.2, J102.2, J102.9, J102.10, J102.11, J102.12, J102.13, SW101.C, SW101.S2
unnamed: R101.1, R103.2, SW101.A
unnamed: R102.1, R104.2, SW101.B

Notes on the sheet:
Waveshare 2inch ST7789 Display
IDC Connector for BOM 16P 2Rows 2,54mm Pitch

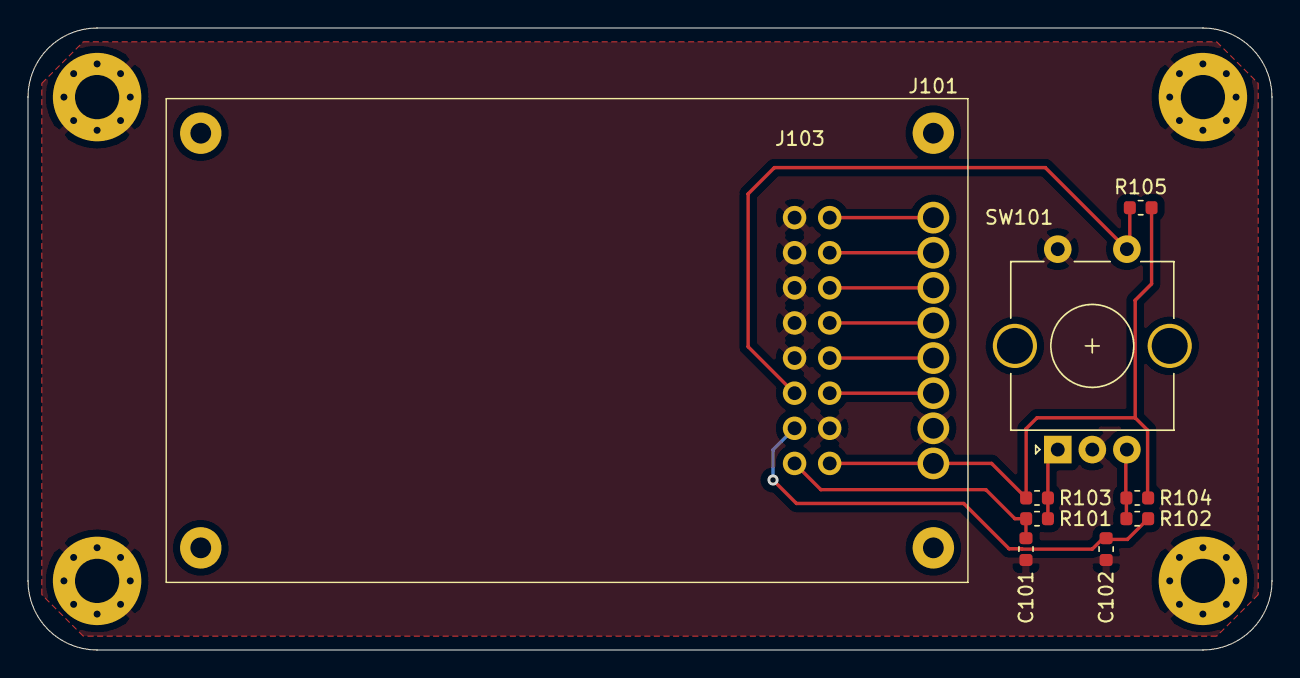
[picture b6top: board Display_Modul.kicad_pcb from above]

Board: 2 copper layers, 90.0 x 45.0 mm, 15 parts (1 on the bottom side), 13 nets.
